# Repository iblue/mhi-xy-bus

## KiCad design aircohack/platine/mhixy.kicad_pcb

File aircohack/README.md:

# MHI X-Y Bus Reverse Engineering Project

This directory contains research and development files for reverse engineering the Mitsubishi Heavy Industries (MHI) air conditioning X-Y bus communication protocol.

## Project Status

**This project was never completed.** The files are published in the hope that they may be useful to someone interested in the specifics of the MHI X-Y bus protocol. The protocol analysis is partially complete, and the hardware designs reached prototype stage but were not finalized.

## Applicable Devices

This research was conducted on the following MHI equipment:

- **FDUM71VF** - Ducted indoor unit (address 0x0007 on the bus)
- **RC-E5** - Wired remote controller (address 0x8001 on the bus)

The X-Y bus is used across the MHI S-Series air conditioning systems and likely other MHI product lines that use wired remote controllers.

## Project Overview

The MHI X-Y bus is a two-wire communication bus used between MHI air conditioning units and their remote controllers. This project documents the protocol analysis, circuit simulations, and hardware development for interfacing with this bus.

### Key Findings

- **Bus Voltage:** ~17V DC (polarity-independent)
- **Encoding:** 8-level pulse position modulation (3 bits per symbol)
- **Symbol Rate:** ~800 symbols/sec (2400 bits/sec effective)
- **Packet Size:** 48 symbols per packet
- **Timing:** 1247 us per symbol, 50 us pulse width

## Directory Structure

### Documentation

| File | Description |
|------|-------------|
| `info.txt` | Basic bus specifications (German) |
| `notes.txt` | Detailed protocol analysis notes with timing measurements |
| `arduino.txt` | Arduino implementation notes and timing calculations |
| `input.txt` | Analog input circuit design notes |
| `keepalive.txt` | Analysis of keepalive/status packets with counter patterns |
| `parsing.txt` | Detailed packet parsing and field analysis |
| `report.odt` / `report.pdf` | Project report documents |

### Decoder Tools

| File | Description |
|------|-------------|
| `decoder` | Ruby script to decode logic analyzer exports |
| `pwlconvert` | Ruby script for PWL (Piece-Wise Linear) conversion |
| `*.decoded` | Decoded packet capture files |

### LTspice Circuit Simulations

The `.asc` files are LTspice schematic files. The `.log` files contain simulation logs.

| Circuit Family | Description |
|----------------|-------------|
| `Driver*.asc` | Output driver circuit iterations (A1-A8, B1-B4, C1-C14, D1-D2) |
| `Pegelkonverter*.asc` | Level converter circuits (voltage level shifting) |
| `VoltageDoubler*.asc` | Voltage doubler circuits for bus driving |
| `Filter*.asc` | Input filter designs |
| `Konverter_ganzneu*.asc` | Complete converter designs |
| `mosswitch*.asc` | MOSFET switching circuit designs |
| `Ausgangstreiber.asc` | Output driver (German: "Ausgangstreiber") |
| `Disconnector.asc` | Bus disconnect circuit |
| `MCDriverVDouble.asc` | Microcontroller driver with voltage doubler |
| `Final-*.asc` | Final circuit revisions |

### Component Libraries

| File | Description |
|------|-------------|
| `7805.asy` / `7812.asy` | LTspice symbols for 7805/7812 voltage regulators |
| `LM339.sub` | LTspice subcircuit for LM339 comparator |
| `LM393.5_1` | LTspice model for LM393 comparator |
| `regulators.lib` | Voltage regulator library |

### Hardware Design (KiCad)

The `platine/` directory contains KiCad PCB design files:

| File | Description |
|------|-------------|
| `mhixy.sch` | Main schematic |
| `mhixy.kicad_pcb` | PCB layout |
| `mhixy.pro` | KiCad project file |
| `*.sch` | Sub-schematics (ChargePump, Controller, Generators, InputConverter, InputVoltageFilter, OutputDriver) |
| `gerber-f3b1-3/` | Gerber files for PCB manufacturing |
| `ReicheltBOM.csv` | Bill of materials (Reichelt supplier format) |

### Microcontroller Firmware

The `reader/` directory contains AVR microcontroller firmware for reading the bus:

| File | Description |
|------|-------------|
| `main.c` / `main.h` | Main firmware source |
| `uart.c` / `uart.h` | UART communication driver |
| `ringbuffer.c` / `ringbuffer.h` | Ring buffer implementation |
| `panic.c` / `panic.h` | Error handling |
| `Makefile` | Build configuration |
| `main.hex` | Compiled firmware |
| `decoder` | Host-side decoder for serial data |
| `reader*.log` | Captured bus data logs |
| `datablock.txt` / `datablock-interpretation.txt` | Protocol field analysis |

### Miscellaneous

| File | Description |
|------|-------------|
| `output/` | Output directory (empty) |
| `pwl-out.txt` | PWL output file |

## Protocol Summary

### Packet Structure

Each packet contains 48 symbols (144 bits). The encoding uses pulse position modulation where the time between a low pulse and the following high pulse encodes 3 bits:

| Time (us) | Value |
|-----------|-------|
| ~100 | 0 |
| ~200 | 1 |
| ~300 | 2 |
| ~400 | 3 |
| ~500 | 4 |
| ~600 | 5 |
| ~700 | 6 |
| ~800 | 7 |

### Communication Pattern

1. Remote controller sends status packet
2. AC unit responds with ACK
3. Cycle repeats every ~5 seconds

### Identified Packet Types

- **Status packets:** Regular keepalive with incrementing counters
- **Command packets:** On/off, temperature changes
- **ACK packets:** Acknowledgment from AC unit

## Regenerating Simulation Data

The `.raw` simulation output files have been removed to reduce repository size. To regenerate them:

1. Open any `.asc` file in LTspice
2. Run the simulation (Run > Run or press the play button)
3. The `.raw` file will be generated automatically

## Requirements

- **LTspice:** For viewing and simulating circuit designs
- **KiCad:** For viewing PCB designs (in `platine/`)
- **Ruby:** For running decoder scripts
- **AVR toolchain:** For compiling firmware (in `reader/`)

## License

This is a reverse engineering research project, approved for public release. Use at your own risk.

## Credits

Original research by Markus Fenske / exablue GmbH (2018).

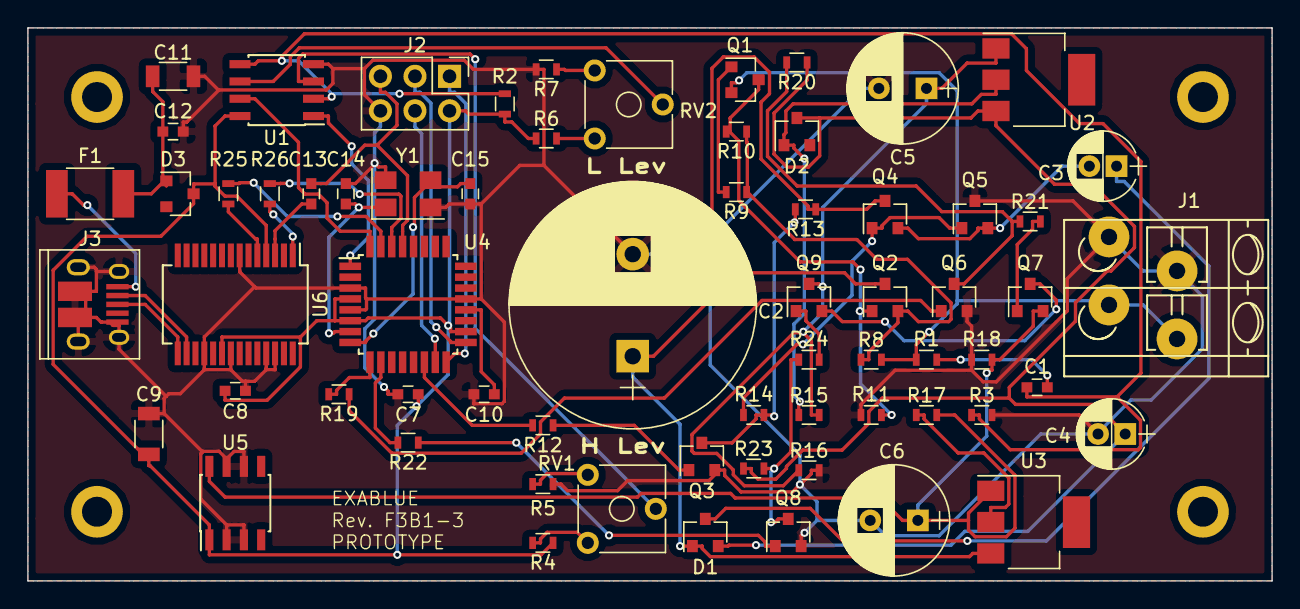
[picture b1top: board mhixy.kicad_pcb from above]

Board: 2 copper layers, 91.4 x 40.6 mm, 70 parts (0 on the bottom side), 53 nets.

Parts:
C1: 47n; C_0603
C2: 4700u; CP_Radial_D18.0mm_P7.50mm
C3, C4: 22u; CP_Radial_D5.0mm_P2.00mm
C5, C6: 100u; CP_Radial_D8.0mm_P3.50mm
C7, C8: 1u; C_0603
C9, C11: 4u7; C_1206
C10, C12, C13: 100n; C_0603
C14, C15: 12p; C_0603
D1: BAT54S; SOT-23
D2, D3: BAT54; D_SOT-23_ANK
F1: Polyfuse; R_1812
H1, H2, H3, H4: MountingHole_2.2mm_M2_DIN965_Pad
J1: MHI Bus; TerminalBlock_WAGO-804_RM5mm_2pol
J2: ISP; Pin_Header_Straight_2x03_Pitch2.54mm
J3: USB_OTG; USB_Micro-B_10103594-0001LF
Q1: BC857A; SOT-23
Q2, Q5, Q7, Q9: BC807-40; SOT-23
Q3, Q6, Q8: BC847C; SOT-23
Q4: BC817-40; SOT-23
R1: 47k; R_0603
R2, R3, R11: 220k; R_0603
R4, R5, R6, R7: 25k; R_0603
R8: 1; R_0603
R9: 2k2; R_0603
R10: 22k; R_0603
R12, R13, R19, R21, R22, R24: 10k; R_0603
R14, R25, R26: 1k; R_0603
R15, R17: 220; R_0603
R16: 3k9; R_0603
R18: 1k8; R_0603
R20, R23: 100k; R_0603
RV1, RV2: 50k; Potentiometer_Trimmer_ACP_CA6v_Horizontal
U1: LM358; SOIC-8_3.9x4.9mm_Pitch1.27mm
U2, U3: LM317M; SOT-223
U4: ATMEGA328-AU; TQFP-32_7x7mm_Pitch0.8mm
U5: 78L05; SOIC-8_3.9x4.9mm_Pitch1.27mm
U6: FT232RL; SSOP-28_5.3x10.2mm_Pitch0.65mm
Y1: 16MHz; Crystal_SMD_5032-4pin_5.0x3.2mm

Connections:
+5V: C7.1, C8.1, C9.1, D3.1, J2.2, R2.1, R4.1, R6.1, U1.8, U4.4, U4.6, U4.18, U5.1, U6.4, U6.20
/ChargePump/17V: C2.1, D1.1, Q2.3, Q4.3, R13.1, U3.3
/ChargePump/32V: C4.1, D1.2, D2.1, R20.1, R23.1, U2.3
/ChargePump/CLK: R12.2, U4.14
/Controller/RXHI: U1.1, U4.1
/Controller/RXLO: U1.7, U4.32
/Generators/12V: C6.1, Q7.2, R17.2, R18.1, U3.1, U5.8
/Generators/22V: C5.1, Q9.3, R15.2, R16.1, U2.1
/OutputDriver/BusOut: Q7.3, Q9.2
/OutputDriver/TTLInHigh: R22.2, U4.10
/OutputDriver/TTLInLow: R19.2, U4.9
Bus: J1.1, Q1.2, R1.2, R8.2
Filtered: C1.1, R2.2, R3.1, U1.2, U1.5
GND: C2.2, C4.2, C5.2, C6.2, C7.2, C8.2, C9.2, C10.2, C11.2, C12.2, C14.1, C15.1, J1.2, J2.6, J3.5, J3.6, Q3.2, Q5.3, Q6.2, Q8.2, R3.2, R5.2, R7.2, R11.2, R16.2, R18.2, U1.4, U4.3, U4.5, U4.21, U5.2, U5.3, U5.6, U5.7, U6.7, U6.18, U6.21, U6.25, U6.26, Y1.2, Y1.4
MISO: J2.1, U4.16
MOSI: J2.4, U4.15
unnamed: C1.2, R1.1
unnamed: C3.1, D1.3
unnamed: C3.2, Q4.2, Q5.2
unnamed: C10.1, U4.20
unnamed: C11.1, C12.1, D3.2, F1.1
unnamed: C13.2, U6.3
unnamed: C14.2, U4.7, Y1.1
unnamed: C15.2, U4.8, Y1.3
unnamed: D2.2, R15.1, U2.2
unnamed: F1.2, J3.1
unnamed: J3.2, U6.16
unnamed: J3.3, U6.15
unnamed: Q1.1, R9.2
unnamed: Q1.3, Q2.1, R10.2, R11.1
unnamed: Q2.2, R8.1, R9.1, R10.1
unnamed: Q3.1, R12.1
unnamed: Q3.3, R13.2, R14.2
unnamed: Q4.1, Q5.1, R14.1
unnamed: Q6.1, R19.1
unnamed: Q6.3, R20.2, R21.1
unnamed: Q7.1, R21.2
unnamed: Q8.1, R22.1
unnamed: Q8.3, R23.2, R24.1
unnamed: Q9.1, R24.2
unnamed: R4.2, RV1.1
unnamed: R5.1, RV1.3
unnamed: R6.2, RV2.1
unnamed: R7.1, RV2.3
unnamed: R17.1, U3.2
unnamed: R25.2, U4.31
unnamed: R26.2, U4.30
unnamed: RV1.2, U1.3
unnamed: RV2.2, U1.6
RESET: C13.1, J2.5, U4.29
RX: R26.1, U6.1
SCK: J2.3, U4.17
TX: R25.1, U6.5

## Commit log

2023-10-31 Add Reverse Engineering Project Report DRAFT
    In the hope that it may help someone.
2026-01-11 Add experimental project data
2026-01-11 Add README.md
2026-01-11 Move README.md to root
